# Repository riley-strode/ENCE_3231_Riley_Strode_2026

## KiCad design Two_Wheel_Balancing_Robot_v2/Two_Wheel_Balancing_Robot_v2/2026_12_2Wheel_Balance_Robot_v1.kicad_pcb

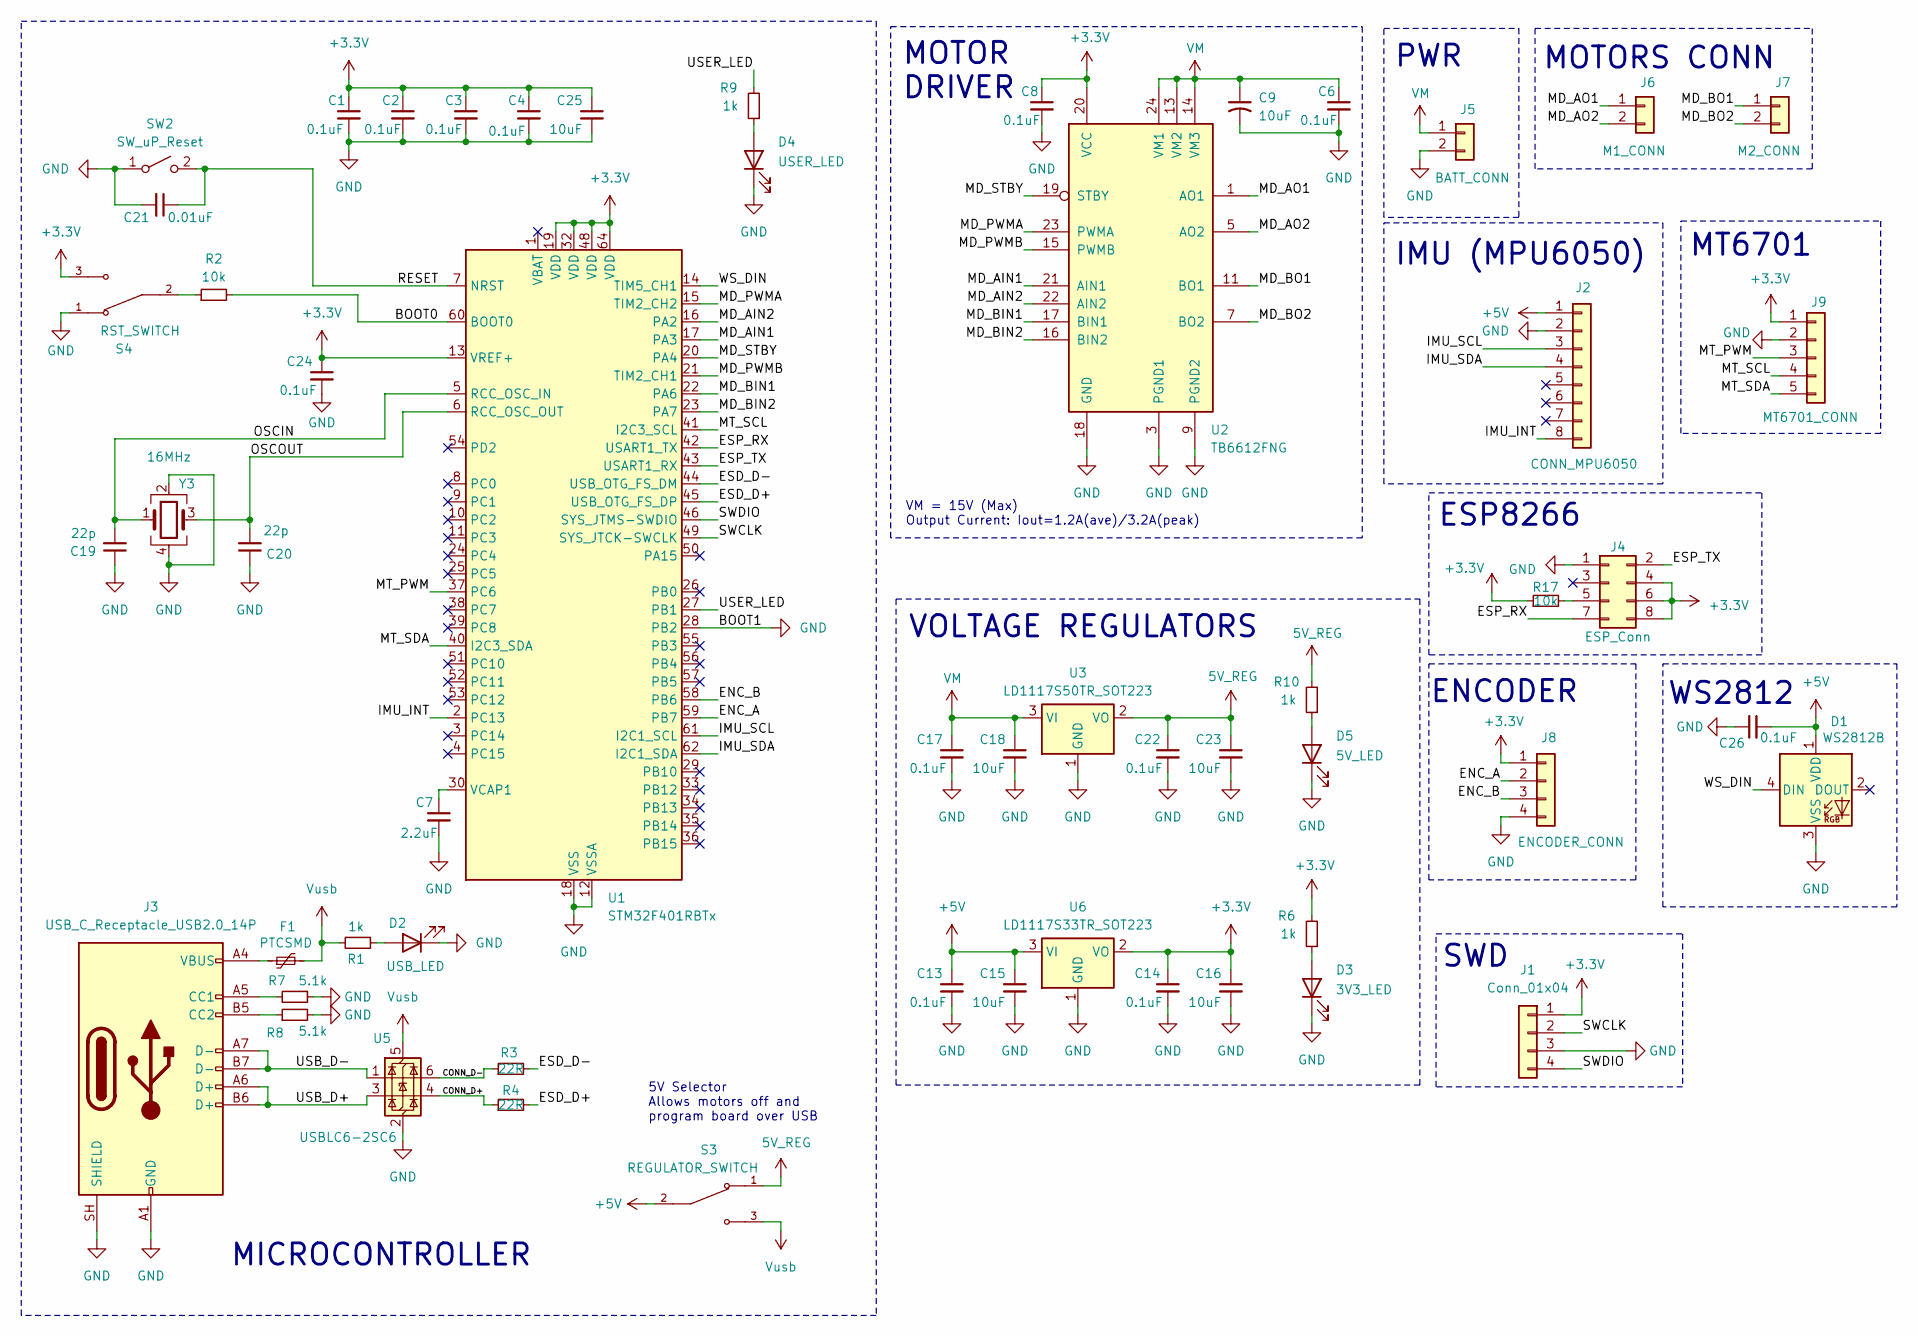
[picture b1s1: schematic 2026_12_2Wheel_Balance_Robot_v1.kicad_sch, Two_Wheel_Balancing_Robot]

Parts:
C1, C2, C3, C4, C6, C8, C13, C14, C17, C22, C24, C26: 0.1uF; C_0805_2012Metric_Pad1.18x1.45mm_HandSolder; Mfr # C0805C104K4JACAUTO
C7: 2.2uF; C_0805_2012Metric_Pad1.18x1.45mm_HandSolder; Mfr # C0805X225K3RACAUTO
C9: 10uF; CP_EIA-6032-28_Kemet-C_HandSolder; Mfr # TPSC106M025R0500
C15, C16, C18, C23: 10uF; C_0805_2012Metric_Pad1.18x1.45mm_HandSolder; Mfr # C0805C106K4PACTU
C19, C20: 22p; C_0805_2012Metric_Pad1.18x1.45mm_HandSolder; Mfg Part# 08055C220KAT2A
C21: 0.01uF; C_0805_2012Metric_Pad1.18x1.45mm_HandSolder; Mfg Part# KAF21BR72A103JT
C25: 10uF; C_0805_2012Metric_Pad1.18x1.45mm_HandSolder; Mfg Part# C0805C106K4PACTU
D1: WS2812B; LED_WS2812B_PLCC4_5.0x5.0mm_P3.2mm; Mfr # FZ2812-5050; Mouser Digikey Part
D2: USB_LED; LED_0805_2012Metric_Pad1.15x1.40mm_HandSolder; Mfr # 150080BS75000
D3: 3V3_LED; LED_0805_2012Metric_Pad1.15x1.40mm_HandSolder; Mfr # 150080BS75000
D4: USER_LED; LED_0805_2012Metric_Pad1.15x1.40mm_HandSolder; Mfr # 150080BS75000
D5: 5V_LED; LED_0805_2012Metric_Pad1.15x1.40mm_HandSolder; Mfr # 150080BS75000
F1: PTCSMD; Fuse_1812_4532Metric; Mfr # MF-MSMF050-2
J1: Conn_01x04; PinHeader_1x04_P2.54mm_Vertical
J2: CONN_MPU6050; PinSocket_1x08_P2.54mm_Vertical
J3: USB_C_Receptacle_USB2.0_14P; USB_C_Receptacle_HCTL_HC-TYPE-C-16P-01A; Mfg Part# UJ20-C-H-C-4-SMT-TR
J4: ESP_Conn; PinSocket_2x04_P2.54mm_Vertical
J5: BATT_CONN; JST_XH_B2B-XH-A_1x02_P2.50mm_Vertical
J6: M1_CONN; JST_XH_B2B-XH-A_1x02_P2.50mm_Vertical
J7: M2_CONN; JST_XH_B2B-XH-A_1x02_P2.50mm_Vertical
J8: ENCODER_CONN; JST_XH_B4B-XH-A_1x04_P2.50mm_Vertical
J9: MT6701_CONN; JST_XH_B5B-XH-A_1x05_P2.50mm_Vertical
R1, R6, R9, R10: 1k; R_0805_2012Metric_Pad1.20x1.40mm_HandSolder; Mfr # TNPW08051K00FEEA
R2, R17: 10k; R_0805_2012Metric_Pad1.20x1.40mm_HandSolder; Mfr # CPF0805B10KE1
R3, R4: 22R; R_0805_2012Metric_Pad1.20x1.40mm_HandSolder; Mfr # RCA080522R0FKEA
R7, R8: 5.1k; R_0603_1608Metric_Pad0.98x0.95mm_HandSolder; Mfg Part# CRCW06035K10FKEC
S3: REGULATOR_SWITCH; SW_SLW-66527511-SMT-TR; PARTREV 1.01
S4: RST_SWITCH; SW_SLW-66527511-SMT-TR; PARTREV 1.01
SW2: SW_uP_Reset; Mfg Part# 434121025816
U1: STM32F401RBTx; LQFP-64_10x10mm_P0.5mm; Mfr # STM32F401RBT6
U2: TB6612FNG; SSOP-24_5.3x8.2mm_P0.65mm; Mfr # TB6612FNG,C,8,EL
U3: LD1117S50TR_SOT223; SOT-223-3_TabPin2; Mfr # LD1117S50TR
U5: USBLC6-2SC6; SOT-23-6; Mfr # USBLC6-2SC6
U6: LD1117S33TR_SOT223; SOT-223-3_TabPin2; Mfr # LD1117S33TR
Y3: 16MHz; Crystal_SMD_Abracon_ABM8G-4Pin_3.2x2.5mm; Mfg Part# ABM8-16.000MHZ-D1X-T

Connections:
5V_REG: C22.1, C23.1, R10.2, S3.1, U3.2 (VO)
+3.3V: C1.1, C2.1, C3.1, C4.1, C8.1, C14.1, C16.1, C24.1, C25.1, J1.1, J4.4, J4.6, J4.8, J8.1, J9.1, R6.2, R17.1, S4.3, U1.13 (VREF+), U1.19 (VDD), U1.32 (VDD), U1.48 (VDD), U1.64 (VDD), U2.20 (VCC), U6.2 (VO)
+5V: C13.1, C15.1, C26.2, D1.1 (VDD), J2.1, S3.2, U6.3 (VI)
/BOOT0: R2.2, U1.60 (BOOT0)
/CONN_D+: R4.1, U5.4 (I/O2)
/CONN_D-: R3.1, U5.6 (I/O1)
/ENC_A: J8.2, U1.59 (PB7)
/ENC_B: J8.3, U1.58 (PB6)
/ESD_D+: R4.2, U1.45 (USB_OTG_FS_DP)
/ESD_D-: R3.2, U1.44 (USB_OTG_FS_DM)
/ESP_RX: J4.7, U1.42 (USART1_TX)
/ESP_TX: J4.2, U1.43 (USART1_RX)
/IMU_INT: J2.8, U1.2 (PC13)
/IMU_SCL: J2.3, U1.61 (I2C1_SCL)
/IMU_SDA: J2.4, U1.62 (I2C1_SDA)
/MD_AIN1: U1.17 (PA3), U2.21 (AIN1)
/MD_AIN2: U1.16 (PA2), U2.22 (AIN2)
/MD_AO1: J6.1, U2.1 (AO1), U2.2 (AO1)
/MD_AO2: J6.2, U2.5 (AO2), U2.6 (AO2)
/MD_BIN1: U1.22 (PA6), U2.17 (BIN1)
/MD_BIN2: U1.23 (PA7), U2.16 (BIN2)
/MD_BO1: J7.1, U2.11 (BO1), U2.12 (BO1)
/MD_BO2: J7.2, U2.7 (BO2), U2.8 (BO2)
/MD_PWMA: U1.15 (TIM2_CH2), U2.23 (PWMA)
/MD_PWMB: U1.21 (TIM2_CH1), U2.15 (PWMB)
/MD_STBY: U1.20 (PA4), U2.19 (STBY)
/MT_PWM: J9.3, U1.37 (PC6)
/MT_SCL: J9.4, U1.41 (I2C3_SCL)
/MT_SDA: J9.5, U1.40 (I2C3_SDA)
/OSCIN: C19.2, U1.5 (RCC_OSC_IN), Y3.1
/OSCOUT: C20.2, U1.6 (RCC_OSC_OUT), Y3.3
/RESET: C21.1, SW2.2 (B), U1.7 (NRST)
/SWCLK: J1.2, U1.49 (SYS_JTCK-SWCLK)
/SWDIO: J1.4, U1.46 (SYS_JTMS-SWDIO)
/USB_D+: J3.A6 (D+), J3.B6 (D+), U5.3 (I/O2)
/USB_D-: J3.A7 (D-), J3.B7 (D-), U5.1 (I/O1)
/USER_LED: R9.2, U1.27 (PB1)
/WS_DIN: D1.4 (DIN), U1.14 (TIM5_CH1)
GND: C1.2, C2.2, C3.2, C4.2, C6.2, C7.2, C8.2, C9.2, C13.2, C14.2, C15.2, C16.2, C17.2, C18.2, C19.1, C20.1, C21.2, C22.2, C23.2, C24.2, C25.2, C26.1, D1.3 (VSS), D2.1 (K), D3.1 (K), D4.1 (K), D5.1 (K), J1.3, J2.2, J3.A1 (GND), J3.A12 (GND), J3.B1 (GND), J3.B12 (GND), J3.SH (SHIELD), J4.1, J5.2, J8.4, J9.2, R7.1, R8.2, S4.1, SW2.1 (A), U1.12 (VSSA), U1.18 (VSS), U1.28 (PB2), U1.31 (VSS), U1.47 (VSS), U1.63 (VSS), U2.3 (PGND1), U2.4 (PGND1), U2.9 (PGND2), U2.10 (PGND2), U2.18 (GND), U3.1 (GND), U5.2 (GND), U6.1 (GND), Y3.2, Y3.4
unnamed: D2.2 (A), R1.1
unnamed: D3.2 (A), R6.1
unnamed: D4.2 (A), R9.1
unnamed: D5.2 (A), R10.1
unnamed: F1.1, J3.A4 (VBUS), J3.A9 (VBUS), J3.B4 (VBUS), J3.B9 (VBUS)
unnamed: J3.A5 (CC1), R7.2
unnamed: J3.B5 (CC2), R8.1
unnamed: J4.5, R17.2
unnamed: R2.1, S4.2
unnamed: C7.1, U1.30 (VCAP1)
VM: C6.1, C9.1, C17.1, C18.1, J5.1, U2.13 (VM2), U2.14 (VM3), U2.24 (VM1), U3.3 (VI)
Vusb: F1.2, R1.2, S3.3, U5.5 (VBUS)

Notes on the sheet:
5V Selector Allows motors off and program board over USB
MT6701
SWD
MOTORS CONN
IMU (MPU6050)
MOTOR DRIVER
VOLTAGE REGULATORS
ENCODER
MICROCONTROLLER
PWR
ESP8266
VM = 15V (Max) Output Current: Iout=1.2A(ave)/3.2A(peak)
WS2812

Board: 2 copper layers, 56 parts (0 on the bottom side), 51 nets, no tracks yet.

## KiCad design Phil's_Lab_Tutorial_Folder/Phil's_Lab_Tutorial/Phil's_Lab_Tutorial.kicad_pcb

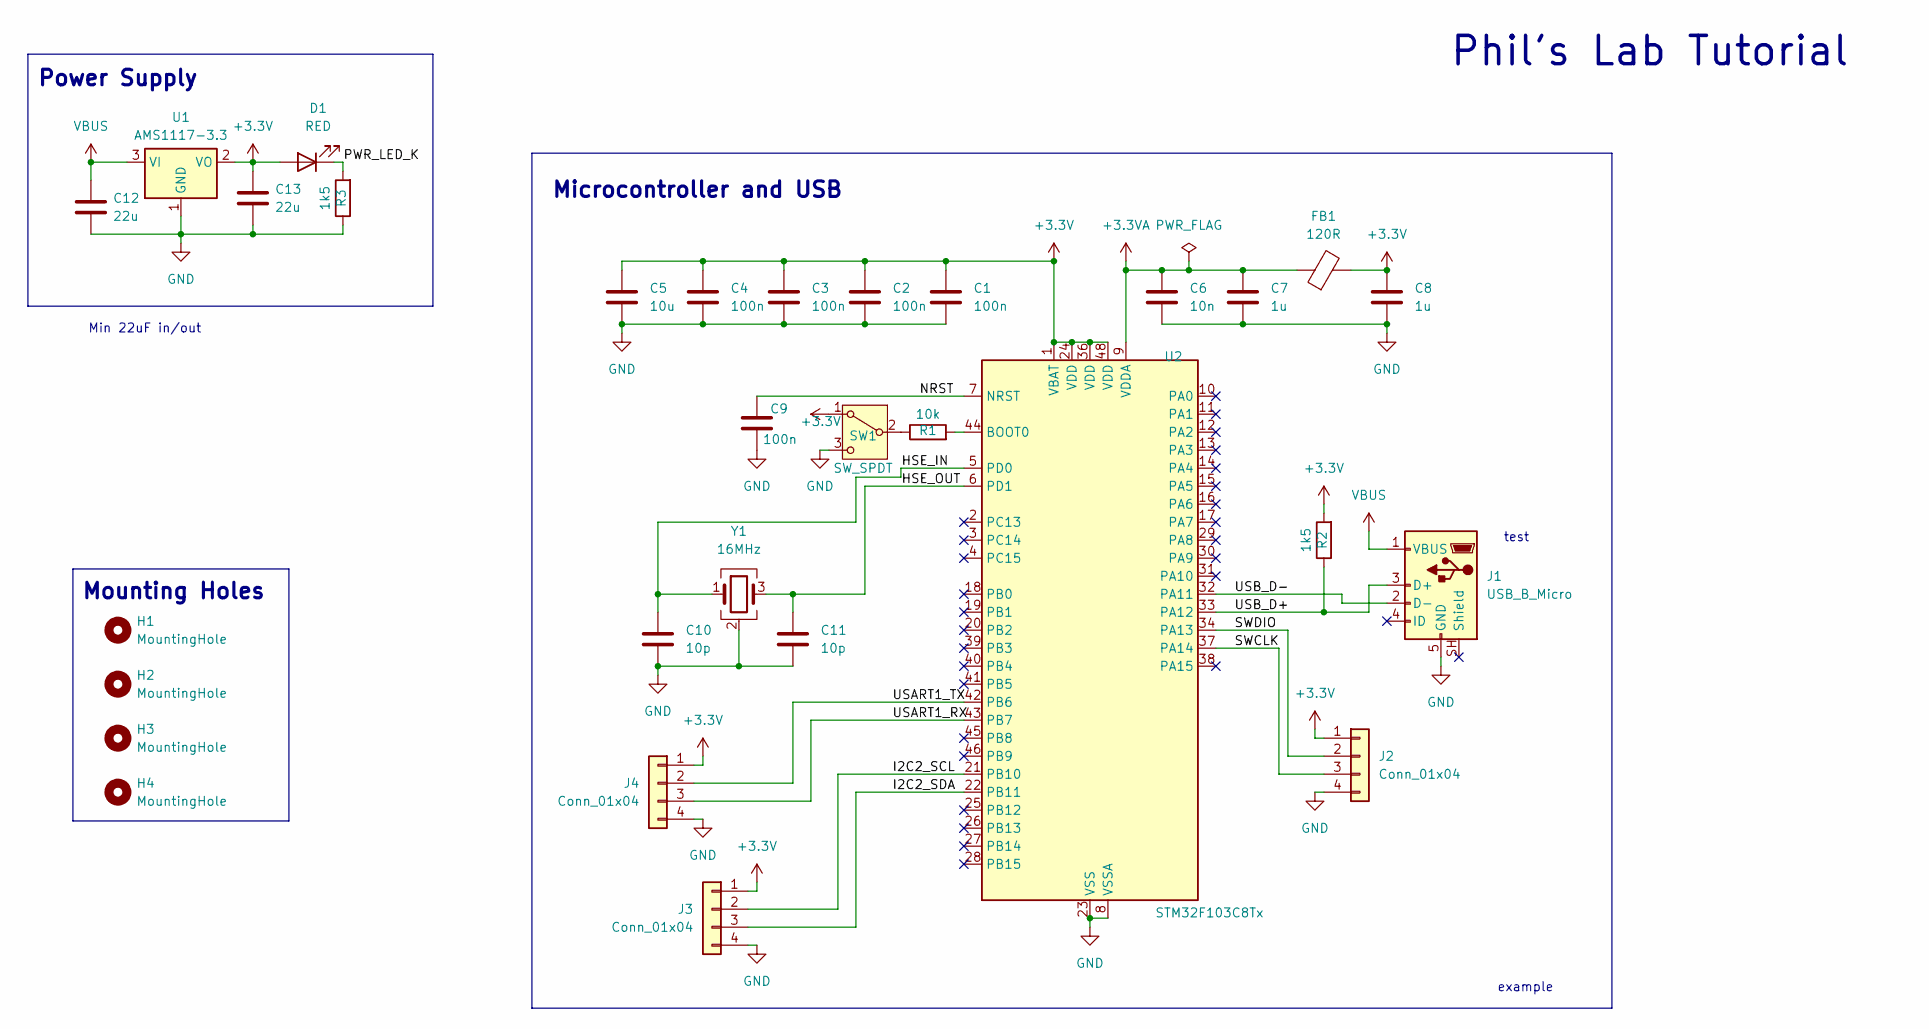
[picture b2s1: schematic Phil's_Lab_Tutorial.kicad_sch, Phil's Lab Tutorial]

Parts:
C1, C2, C3, C4, C9: 100n; C_0402_1005Metric
C5: 10u; C_0603_1608Metric
C6: 10n; C_0603_1608Metric
C7, C8: 1u; C_0402_1005Metric
C10, C11: 10p; C_0402_1005Metric
C12, C13: 22u; C_0805_2012Metric
D1: RED; LED_0603_1608Metric
FB1: 120R; L_0603_1608Metric
H1, H2, H3, H4: MountingHole; MountingHole_2.2mm_M2
J1: USB_B_Micro; USB_Micro-B_Technik_TWP-4002D-H3
J2, J3, J4: Conn_01x04; PinHeader_1x04_P2.54mm_Vertical
R1: 10k; R_0402_1005Metric
R2, R3: 1k5; R_0402_1005Metric
SW1: SW_SPDT; SuperSOT-3
U1: AMS1117-3.3; SOT-223-3_TabPin2
U2: STM32F103C8Tx; LQFP-48_7x7mm_P0.5mm
Y1: 16MHz; Crystal_SMD_3225-4Pin_3.2x2.5mm

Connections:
+3.3V: C1.1, C2.1, C3.1, C4.1, C5.1, C8.1, C13.1, D1.2 (A), FB1.2, J2.1, J3.1, J4.1, R2.2, SW1.1 (A), U1.2 (VO), U2.1 (VBAT), U2.24 (VDD), U2.36 (VDD), U2.48 (VDD)
+3.3VA: C6.1, C7.1, FB1.1, U2.9 (VDDA)
/HSE_IN: C10.1, U2.5 (PD0), Y1.1
/HSE_OUT: C11.1, U2.6 (PD1), Y1.3
/I2C2_SCL: J3.2, U2.21 (PB10)
/I2C2_SDA: J3.3, U2.22 (PB11)
/NRST: C9.1, U2.7 (NRST)
/PWR_LED_K: D1.1 (K), R3.2
/SWCLK: J2.3, U2.37 (PA14)
/SWDIO: J2.2, U2.34 (PA13)
/USART1_RX: J4.3, U2.43 (PB7)
/USART1_TX: J4.2, U2.42 (PB6)
/USB_D+: J1.3 (D+), R2.1, U2.33 (PA12)
/USB_D-: J1.2 (D-), U2.32 (PA11)
GND: C1.2, C2.2, C3.2, C4.2, C5.2, C6.2, C7.2, C8.2, C9.2, C10.2, C11.2, C12.2, C13.2, J1.5 (GND), J2.4, J3.4, J4.4, R3.1, SW1.3 (C), U1.1 (GND), U2.8 (VSSA), U2.23 (VSS), U2.35 (VSS), U2.47 (VSS), Y1.2 (G), Y1.4 (G)
unnamed: R1.1, SW1.2 (B)
unnamed: R1.2, U2.44 (BOOT0)
VBUS: C12.1, J1.1 (VBUS), U1.3 (VI)

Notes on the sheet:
Microcontroller and USB
Mounting Holes
example
Phil's Lab Tutorial
Min 22uF in/out
Power Supply
test

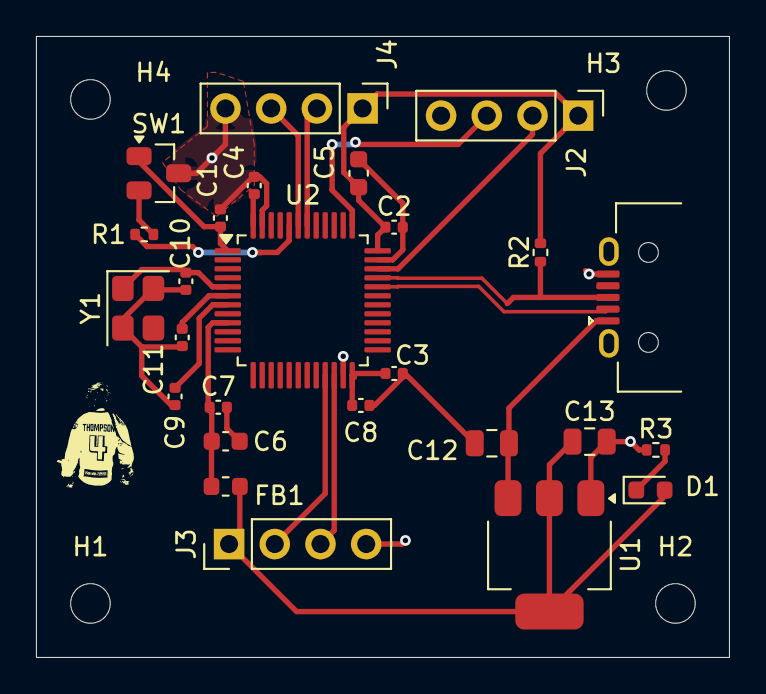
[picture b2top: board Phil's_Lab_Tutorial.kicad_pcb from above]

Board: 2 copper layers, 38.5 x 34.5 mm, 30 parts (0 on the bottom side), 18 nets.

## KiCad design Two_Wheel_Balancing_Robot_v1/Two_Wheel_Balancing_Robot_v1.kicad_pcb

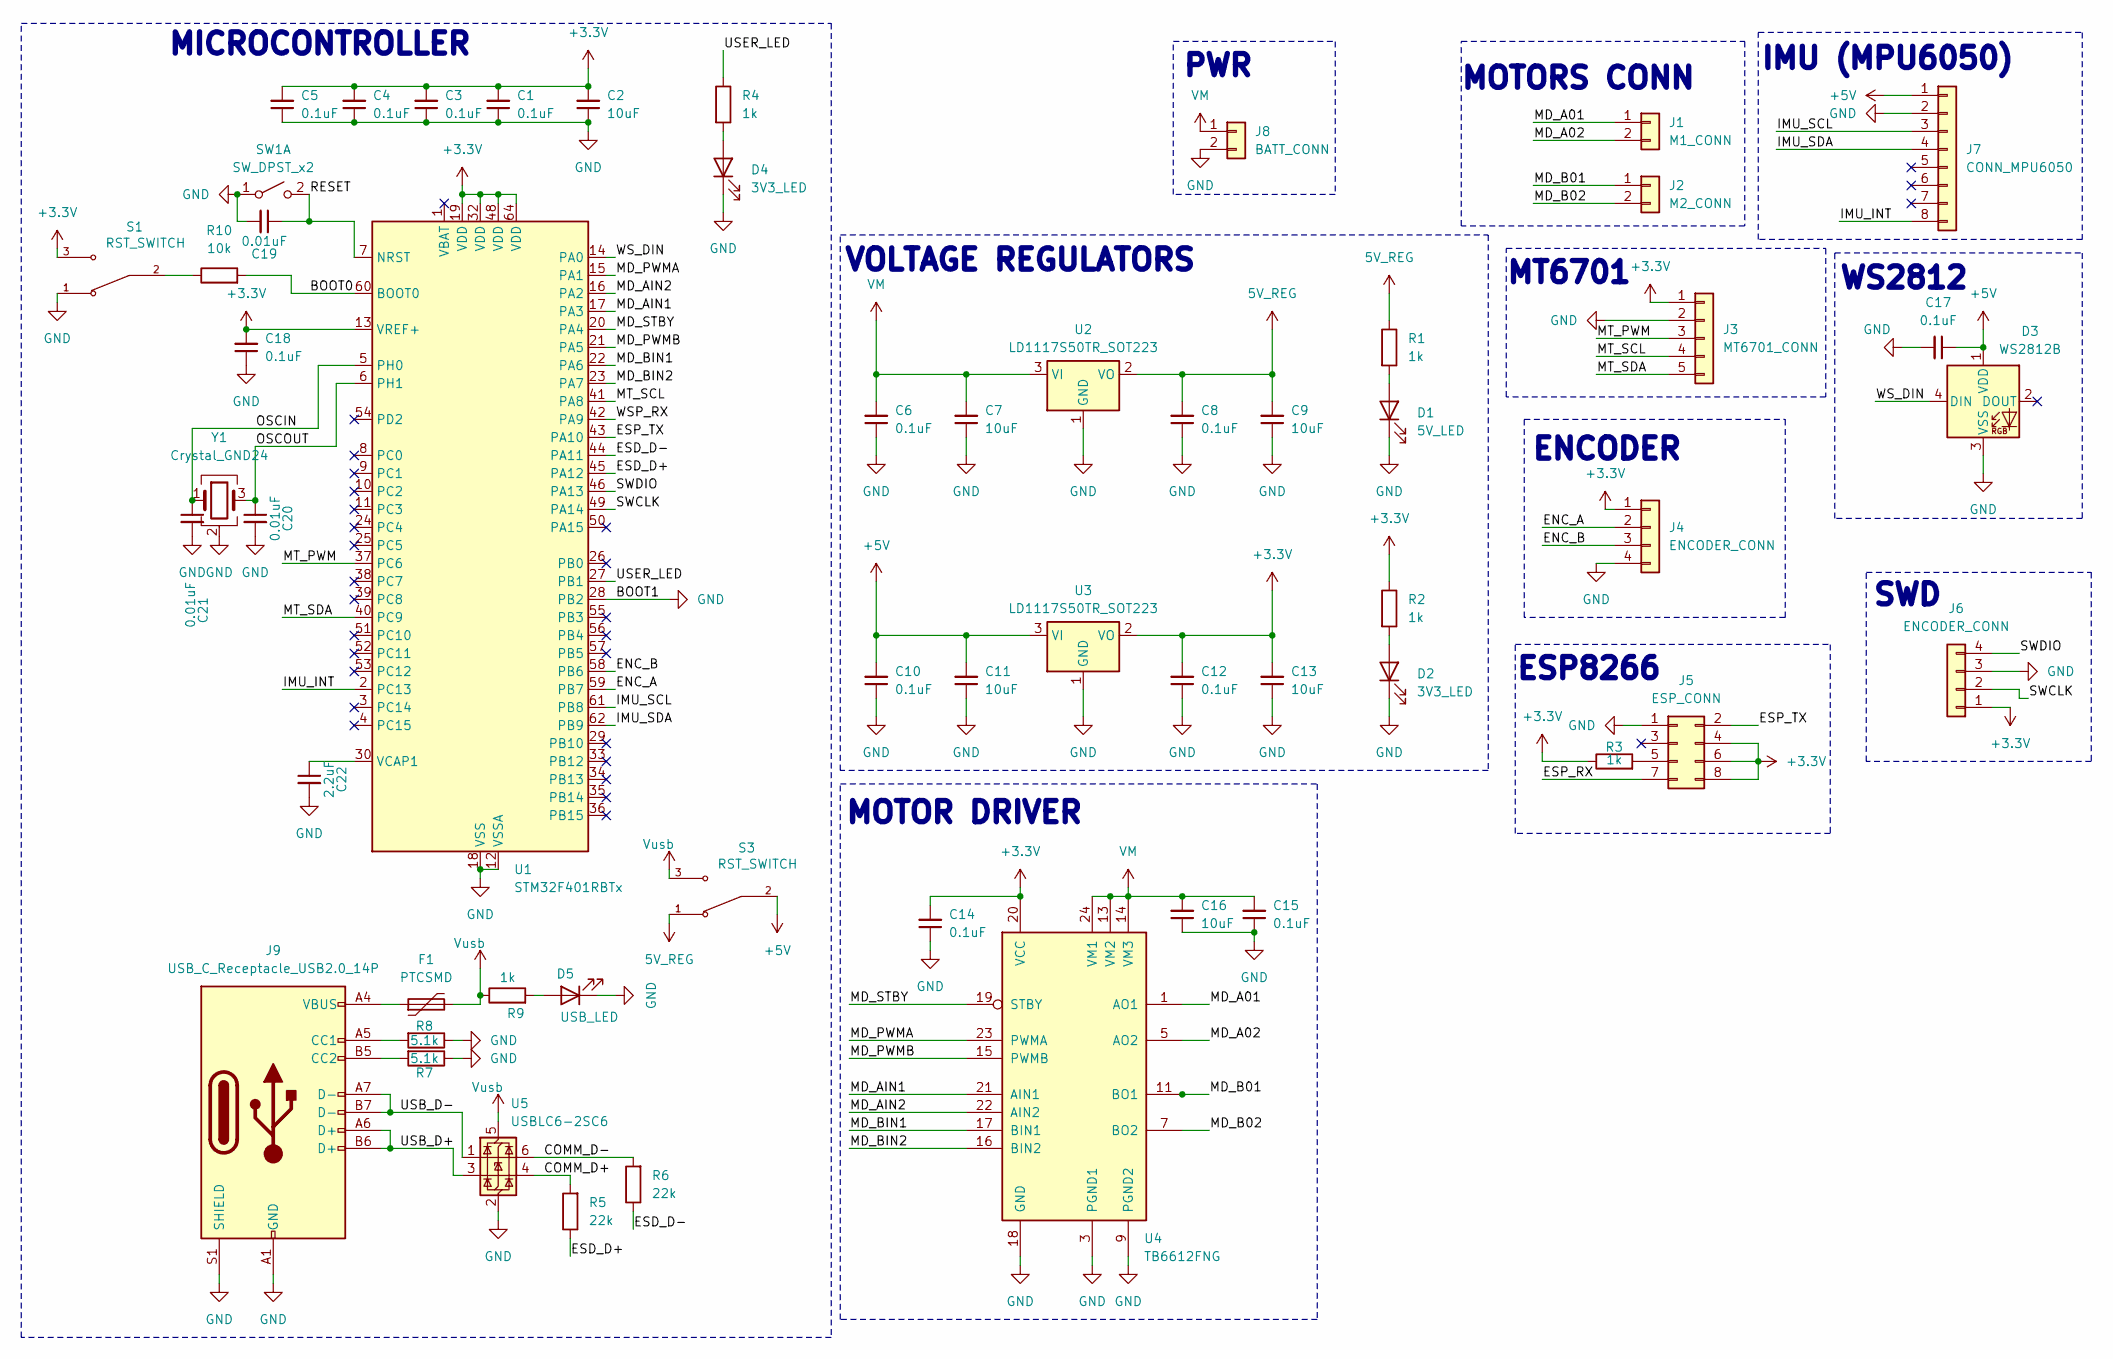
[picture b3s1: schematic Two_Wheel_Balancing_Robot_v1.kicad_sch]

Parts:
C1, C3, C4, C5, C6, C8, C10, C12, C14, C15, C17, C18: 0.1uF; C_0805_2012Metric_Pad1.18x1.45mm_HandSolder; Mfr. # KAM21BR71H104JM
C2, C7, C9, C11, C13, C16: 10uF; C_0805_2012Metric_Pad1.18x1.45mm_HandSolder; Mfr. # CGA4J1X7R0J106K125AC
C19, C20, C21: 0.01uF; C_0805_2012Metric_Pad1.18x1.45mm_HandSolder; Mfr. # KAM21BR71H104JM
C22: 2.2uF; C_0805_2012Metric_Pad1.18x1.45mm_HandSolder; Mfr. # KAM21BR71H104JM
D1: 5V_LED; LED_0805_2012Metric_Pad1.15x1.40mm_HandSolder; Mfr. # LY M676-R2T1-26-Z
D2, D4: 3V3_LED; LED_0805_2012Metric_Pad1.15x1.40mm_HandSolder; Mfr. # LY M676-R2T1-26-Z
D3: WS2812B; LED_WS2812B_PLCC4_5.0x5.0mm_P3.2mm
D5: USB_LED; LED_0805_2012Metric_Pad1.15x1.40mm_HandSolder; Mfr. # LY M676-R2T1-26-Z
F1: PTCSMD; Fuse_1812_4532Metric
J1: M1_CONN; JST_XH_B2B-XH-A_1x02_P2.50mm_Vertical
J2: M2_CONN; JST_XH_B2B-XH-A_1x02_P2.50mm_Vertical
J3: MT6701_CONN; JST_XH_B5B-XH-A_1x05_P2.50mm_Vertical
J4: ENCODER_CONN; JST_XH_B4B-XH-A_1x04_P2.50mm_Vertical
J5: ESP_CONN; PinSocket_2x04_P2.54mm_Vertical
J6: ENCODER_CONN; PinHeader_1x04_P2.54mm_Vertical
J7: CONN_MPU6050; PinSocket_1x08_P2.54mm_Vertical
J8: BATT_CONN; JST_XH_B2B-XH-A_1x02_P2.50mm_Vertical
J9: USB_C_Receptacle_USB2.0_14P; USB_C_Receptacle_HCTL_HC-TYPE-C-16P-01A
R1, R2, R3, R4, R9: 1k; R_0805_2012Metric_Pad1.20x1.40mm_HandSolder; Mfr. # WCR0805LF1001FPLT
R5, R6: 22k; R_0805_2012Metric_Pad1.20x1.40mm_HandSolder; Mfr. # WCR0805LF1001FPLT
R7, R8: 5.1k; R_0805_2012Metric_Pad1.20x1.40mm_HandSolder; Mfr. # WCR0805LF1001FPLT
R10: 10k; R_0805_2012Metric_Pad1.20x1.40mm_HandSolder; Mfr. # WCR0805LF1001FPLT
S1, S3: RST_SWITCH; SW_SLW-66527511-SMT-TR; PARTREV 1.01
SW1: SW_DPST_x2; SW_uP_Reset
U1: STM32F401RBTx; LQFP-64_10x10mm_P0.5mm; Mfr. # STM32F401RET6
U2, U3: LD1117S50TR_SOT223; SOT-223-3_TabPin2
U4: TB6612FNG; SSOP-24_5.3x8.2mm_P0.65mm
U5: USBLC6-2SC6; SOT-23-6
Y1: Crystal_GND24; Crystal_SMD_Abracon_ABM8G-4Pin_3.2x2.5mm

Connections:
5V_REG: C8.2, C9.2, R1.1, S3.1, U2.2 (VO)
+3.3V: C1.2, C2.2, C3.2, C4.2, C5.2, C12.2, C13.2, C14.2, C18.2, J3.1, J4.1, J5.4, J5.6, J5.8, J6.1, R2.1, R3.1, S1.3, U1.13 (VREF+), U1.19 (VDD), U1.32 (VDD), U1.48 (VDD), U1.64 (VDD), U3.2 (VO), U4.20 (VCC)
+5V: C10.2, C11.2, C17.1, D3.1 (VDD), J7.1, S3.2, U3.3 (VI)
/BOOT0: R10.2, U1.60 (BOOT0)
/COMM_D+: R5.2, U5.4 (I/O2)
/COMM_D-: R6.2, U5.6 (I/O1)
/ENC_A: J4.2, U1.59 (PB7)
/ENC_B: J4.3, U1.58 (PB6)
/ESD_D+: R5.1, U1.45 (PA12)
/ESD_D-: R6.1, U1.44 (PA11)
/ESP_RX: J5.7
/ESP_TX: J5.2, U1.43 (PA10)
/IMU_INT: J7.8, U1.2 (PC13)
/IMU_SCL: J7.3, U1.61 (PB8)
/IMU_SDA: J7.4, U1.62 (PB9)
/MD_A01: J1.1, U4.1 (AO1), U4.2 (AO1)
/MD_A02: J1.2, U4.5 (AO2), U4.6 (AO2)
/MD_AIN1: U1.17 (PA3), U4.21 (AIN1)
/MD_AIN2: U1.16 (PA2), U4.22 (AIN2)
/MD_B01: J2.1, U4.11 (BO1), U4.12 (BO1)
/MD_B02: J2.2, U4.7 (BO2), U4.8 (BO2)
/MD_BIN1: U1.22 (PA6), U4.17 (BIN1)
/MD_BIN2: U1.23 (PA7), U4.16 (BIN2)
/MD_PWMA: U1.15 (PA1), U4.23 (PWMA)
/MD_PWMB: U1.21 (PA5), U4.15 (PWMB)
/MD_STBY: U1.20 (PA4), U4.19 (STBY)
/MT_PWM: J3.3, U1.37 (PC6)
/MT_SCL: J3.4, U1.41 (PA8)
/MT_SDA: J3.5, U1.40 (PC9)
/OSCIN: C21.1, U1.5 (PH0), Y1.1
/OSCOUT: C20.1, U1.6 (PH1), Y1.3
/RESET: C19.1, SW1.2 (B), U1.7 (NRST)
/SWCLK: J6.2, U1.49 (PA14)
/SWDIO: J6.4, U1.46 (PA13)
/USB_D+: J9.A6 (D+), J9.B6 (D+), U5.3 (I/O2)
/USB_D-: J9.A7 (D-), J9.B7 (D-), U5.1 (I/O1)
/USER_LED: R4.1, U1.27 (PB1)
/WSP_RX: U1.42 (PA9)
/WS_DIN: D3.4 (DIN), U1.14 (PA0)
GND: C1.1, C2.1, C3.1, C4.1, C5.1, C6.1, C7.1, C8.1, C9.1, C10.1, C11.1, C12.1, C13.1, C14.1, C15.1, C16.1, C17.2, C18.1, C19.2, C20.2, C21.2, C22.2, D1.1 (K), D2.1 (K), D3.3 (VSS), D4.1 (K), D5.1 (K), J3.2, J4.4, J5.1, J6.3, J7.2, J8.2, J9.A1 (GND), J9.A12 (GND), J9.B1 (GND), J9.B12 (GND), J9.S1 (SHIELD), R7.1, R8.1, S1.1, SW1.1 (A), U1.12 (VSSA), U1.18 (VSS), U1.28 (PB2), U1.31 (VSS), U1.47 (VSS), U1.63 (VSS), U2.1 (GND), U3.1 (GND), U4.3 (PGND1), U4.4 (PGND1), U4.9 (PGND2), U4.10 (PGND2), U4.18 (GND), U5.2 (GND), Y1.2 (G), Y1.4 (G)
unnamed: D1.2 (A), R1.2
unnamed: D2.2 (A), R2.2
unnamed: D4.2 (A), R4.2
unnamed: D5.2 (A), R9.2
unnamed: F1.1, J9.A4 (VBUS), J9.A9 (VBUS), J9.B4 (VBUS), J9.B9 (VBUS)
unnamed: J5.5, R3.2
unnamed: J9.A5 (CC1), R8.2
unnamed: J9.B5 (CC2), R7.2
unnamed: R10.1, S1.2
unnamed: C22.1, U1.30 (VCAP1)
VM: C6.2, C7.2, C15.2, C16.2, J8.1, U2.3 (VI), U4.13 (VM2), U4.14 (VM3), U4.24 (VM1)
Vusb: F1.2, R9.1, S3.3, U5.5 (VBUS)

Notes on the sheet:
MT6701
VOLTAGE REGULATORS
WS2812
MICROCONTROLLER
MOTORS CONN
SWD
IMU (MPU6050)
PWR
MOTOR DRIVER
ENCODER
ESP8266

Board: 2 copper layers, 54 parts (0 on the bottom side), 49 nets, no tracks yet.

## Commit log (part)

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2026-04-16 Add files via upload
    All I was able to accomplish was generating the 10 microsecond pulse every 100 microseconds.
2026-04-16 Create Tester_A
    test 1
2026-04-23 Create test
2026-04-28 Create DELETE_LATER
2026-04-30 Create DELETE_ME
2026-06-09 Create testerDELETe
